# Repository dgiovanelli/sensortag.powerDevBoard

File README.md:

# sensortag.powerDevPack

Devboard for adding lipo battery. It features battery charger through micro USB, high efficiency DCDC regulator and UART to USB converter through a FTDI chip. 

It has been designed for cc2650 sensorTag, but it should work also with the other versions till the so called "SKIN" connector keeps the same pinout settings.
The output voltage is fixed by the DCDC to 3.75 volt, it can be reduced acting on the values of RTPS1, RTPS2 and RTPS3. See TPS62737 datasheet for details.
Note that the AON battery monitor won't work because of the DCDC. The battery voltage can be measured usign the appropriate circuit on the powerDevBoard. To activate it set DP2 pin to 'HIGH', then read analog voltage at DP3 pin. The actual battery voltage is twice the voltage measured at DP3. The battery measurement circuit absorbs about 10uA from the battery, when not used set DP2 to "LOW".

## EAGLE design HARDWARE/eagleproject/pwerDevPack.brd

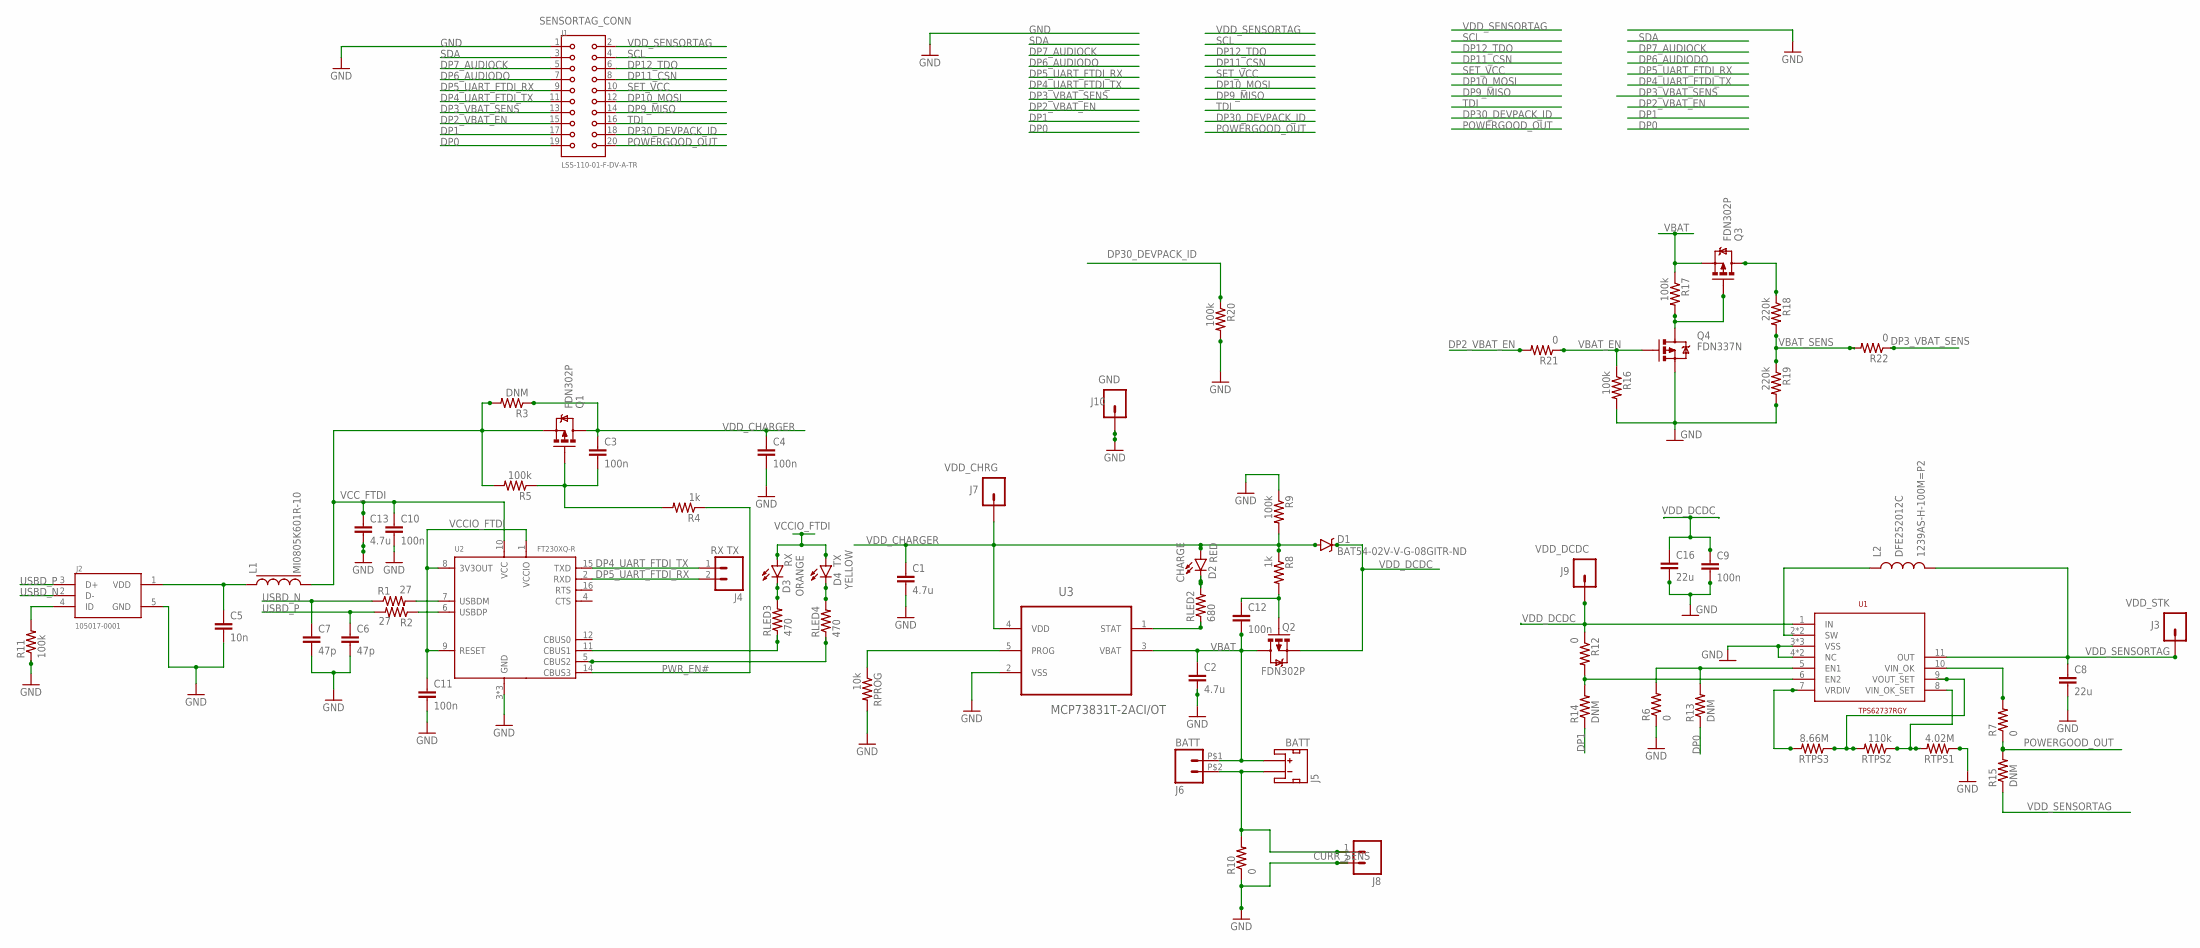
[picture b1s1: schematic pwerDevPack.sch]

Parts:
C1, C2, C13: 4.7u; 0603-CAP
C3, C4, C9, C10, C11, C12: 100n; 0603-CAP
C5: 10n; 0603-CAP
C6, C7: 47p; 0603-CAP
C8, C16: 22u; 0603-CAP
D1: BAT54-02V-V-G-08GITR-ND; SOD-523
D2: RED; LED-0603
D3: ORANGE; LED-0603
D4: YELLOW; LED-0603
J1: LSS-110-01-F-DV-A-TR; SAMTEC_LSS-110-01-F-DV-A-TR
J2: 105017-0001; MOLEX_105017-0001
J3, J7, J9, J10: M01PTH; 1X01
J4, J8: M02PTH; 1X02
J5: S2B-PH-SM4-TB; JST-2-SMD
J6: M02PTH2; 1X02_BIG
L1: MI0805K601R-10; 0805
L2: 1239AS-H-100M=P2; DFE252012C
Q1, Q2, Q3: FDN302P; SOT23-3
Q4: FDN337N; SOT23-3
R1, R2: 27; 0603-RES
R3, R13, R14, R15: DNM; 0603-RES
R4, R8: 1k; 0603-RES
R5, R9, R11, R16, R17, R20: 100k; 0603-RES
R6, R7, R10, R12, R21, R22: 0; 0603-RES
R18, R19: 220k; 0603-RES
RLED2: 680; 0603-RES
RLED3, RLED4: 470; 0603-RES
RPROG: 10k; 0603-RES
RTPS1: 4.02M; 0603-RES
RTPS2: 110k; 0603-RES
RTPS3: 8.66M; 0603-RES
U1: TPS62737RGY; QFN14
U2: FT230XQ-R; QFN16
U3: MCP73831T-2ACI/OT; SOT95P280X145-5N

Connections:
CHARGER_STAT: RLED2.1, U3.1 (STAT)
DP0: J1.19, R13.1
DP1: J1.17, R14.1
DP2_VBAT_EN: J1.15, R21.2
DP3_VBAT_SENS: J1.13, R22.1
DP4_UART_FTDI_TX: J1.11, J4.1, U2.15 (TXD)
DP5_UART_FTDI_RX: J1.9, J4.2, U2.2 (RXD)
DP6_AUDIODO: J1.7
DP7_AUDIOCK: J1.5
DP9_MISO: J1.14
DP10_MOSI: J1.12
DP11_CSN: J1.8
DP12_TDO: J1.6
DP30_DEVPACK_ID: J1.18, R20.1
GND: C1.2, C2.2, C4.2, C5.2, C6.2, C7.2, C8.2, C9.2, C10.2, C11.2, C13.2, C16.2, J1.1, J2.5 (GND), J8.2, J10.1, Q4.2 (S), R6.1, R9.1, R10.1, R11.1, R16.2, R19.2, R20.2, RPROG.2, RTPS1.1, U1.3 (VSS), U1.4 (NC), U1.12 (VSS), U1.14 (NC), U1.TH_PAD (VSS), U2.3 (GND), U2.13 (GND), U2.17 (GND), U3.2 (VSS)
GND_BAT: J5.1 (-), J6.P$2 (2), J8.1, R10.2
unnamed: D3.C, RLED3.2
unnamed: C5.1, J2.1 (VDD), L1.1
unnamed: C3.2, Q1.1 (G), R4.2, R5.1
unnamed: RTPS1.2, RTPS2.1, U1.8 (VIN_OK_SET)
unnamed: R6.2, R13.2, U1.5 (EN1)
unnamed: RPROG.1, U3.5 (PROG)
unnamed: Q3.3 (D), R18.1
unnamed: R12.2, R14.2, U1.6 (EN2)
unnamed: L2.P$1 (1), U1.2 (SW), U1.13 (SW)
unnamed: C12.1, Q2.1 (G), R8.2
unnamed: D2.C, RLED2.2
unnamed: D4.C, RLED4.2
unnamed: Q3.1 (G), Q4.3 (D), R17.2
unnamed: J2.4 (ID), R11.2
unnamed: RLED3.1, U2.11 (CBUS1)
unnamed: R7.2, U1.10 (VIN_OK)
unnamed: RTPS3.2, U1.7 (VRDIV)
unnamed: RLED4.1, U2.5 (CBUS2)
unnamed: RTPS2.2, RTPS3.1, U1.9 (VOUT_SET)
POWERGOOD_OUT: J1.20, R7.1, R15.2
PWR_EN#: R4.1, U2.14 (CBUS3)
SCL: J1.4
SDA: J1.3
SET_VCC: J1.10
TDI: J1.16
USBDR_N: R1.2, U2.7 (USBDM)
USBDR_P: R2.1, U2.6 (USBDP)
USBD_N: C7.1, J2.2 (D-), R1.1
USBD_P: C6.1, J2.3 (D+), R2.2
VBAT: C2.1, C12.2, J5.2 (+), J6.P$1 (1), Q2.3 (D), Q3.2 (S), R17.1, U3.3 (VBAT)
VBAT_EN: Q4.1 (G), R16.1, R21.1
VBAT_SENS: R18.2, R19.1, R22.2
VCCIO_FTDI: C11.1, D3.A, D4.A, U2.1 (VCCIO), U2.8 (3V3OUT), U2.9 (RESET)
VCC_FTDI: C10.1, C13.1, L1.2, Q1.2 (S), R3.2, R5.2, U2.10 (VCC)
VDD_CHARGER: C1.1, C3.1, C4.1, D1.A, D2.A, J7.1, Q1.3 (D), R3.1, R8.1, R9.2, U3.4 (VDD)
VDD_DCDC: C9.1, C16.1, D1.C, J9.1, Q2.2 (S), R12.1, U1.1 (IN)
VDD_SENSORTAG: C8.1, J1.2, J3.1, L2.P$2 (2), R15.1, U1.11 (OUT)

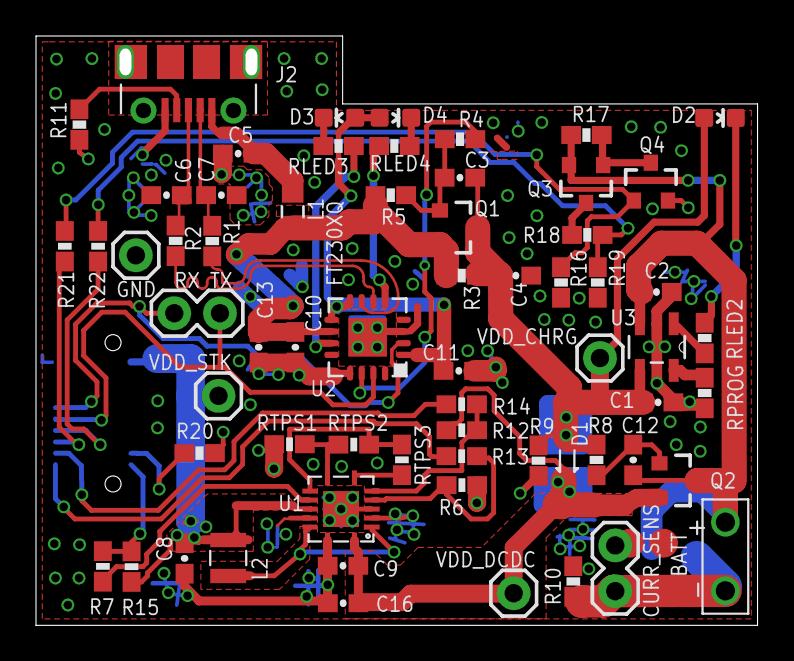
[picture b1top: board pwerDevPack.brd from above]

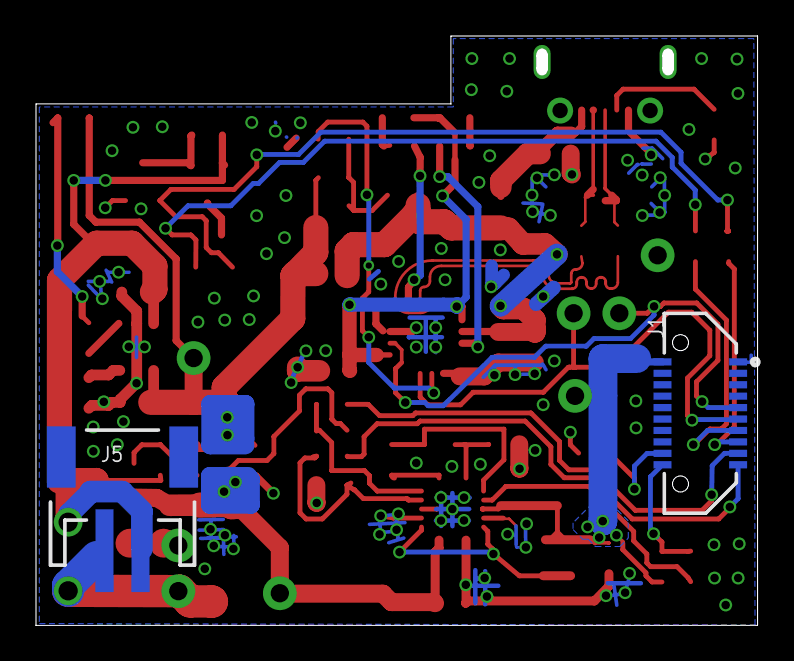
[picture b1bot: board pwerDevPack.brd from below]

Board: 2 copper layers, 39.5 x 32.1 mm, 66 parts (2 on the bottom side), 43 nets.

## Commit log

2017-03-18 First commit. Here the first working version of the board.
    The board has been tested but not extensively.
    Documentation is missing for now.
2017-03-20 Adding schematic and pcb images

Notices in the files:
parts and their libraries:
SparkFun-Capacitors: Licensing: Creative Commons ShareAlike 4.0 International - https://creativecommons.org/licenses/by-sa/4.0
